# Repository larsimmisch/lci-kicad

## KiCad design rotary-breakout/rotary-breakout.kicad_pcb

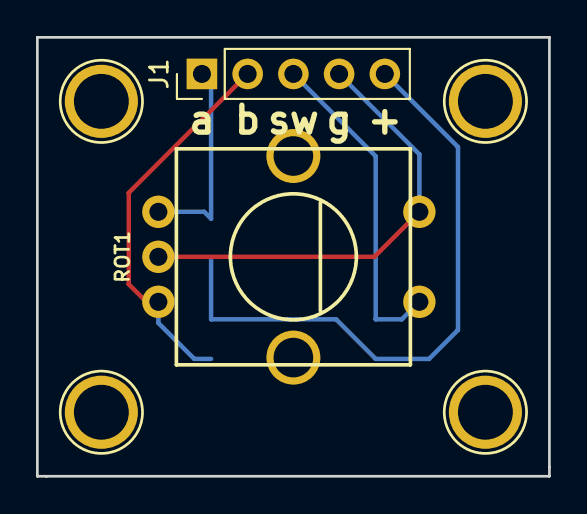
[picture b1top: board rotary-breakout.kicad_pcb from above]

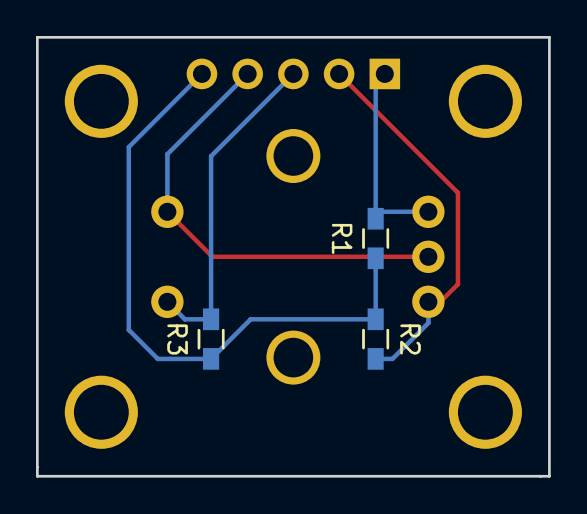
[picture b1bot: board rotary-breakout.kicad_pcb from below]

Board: 2 copper layers, 28.4 x 24.4 mm, 5 parts (3 on the bottom side), 5 nets.

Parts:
J1: CONN_01X05; Pin_Header_Straight_1x05_Pitch2.54mm
R1, R2, R3: R_Small; R_0603_HandSoldering
ROT1: Alps-Rotary-Encoder

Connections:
GND: J1.4, ROT1.1, ROT1.3
unnamed: J1.1, R1.2, ROT1.2
unnamed: J1.2, R2.2, ROT1.4
unnamed: J1.3, R3.2, ROT1.5
VCC: J1.5, R1.1, R2.1, R3.1

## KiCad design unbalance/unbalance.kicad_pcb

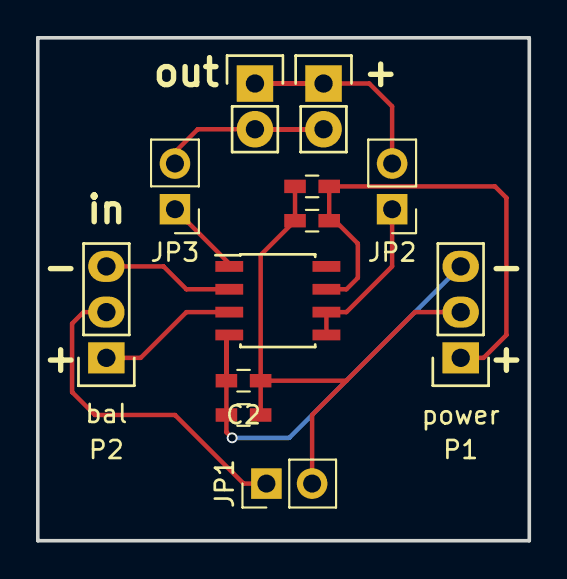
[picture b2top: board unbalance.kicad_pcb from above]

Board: 2 copper layers, 27.3 x 27.9 mm, 12 parts (0 on the bottom side), 10 nets.

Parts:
C1, C2: 1uF; C_0603_HandSoldering
C3, C4: 10uF; C_0603_HandSoldering
JP1: gnd lift; Pin_Header_Straight_1x02_Pitch2.54mm
JP2, JP3: Jumper_NC_Small; Pin_Header_Straight_1x02_Pitch2.54mm
P1: power; Pin_Header_Straight_1x03
P2: bal; Pin_Header_Straight_1x03
P3, P4: CONN_01X02; Pin_Header_Straight_1x02
U1: INA134; SOIC-8_3.9x4.9mm_Pitch1.27mm

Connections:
+15V: C1.1, C3.1, P1.1, U1.7
-15V: C2.2, C4.1, P1.3, U1.4
GNDA: C1.2, C2.1, C3.2, C4.2, JP1.2, P1.2
unnamed: JP1.1, P2.2
unnamed: JP2.1, U1.5, U1.6
unnamed: JP2.2, P3.1, P4.1
unnamed: JP3.1, U1.1
unnamed: JP3.2, P3.2, P4.2
unnamed: P2.1, U1.3
unnamed: P2.3, U1.2

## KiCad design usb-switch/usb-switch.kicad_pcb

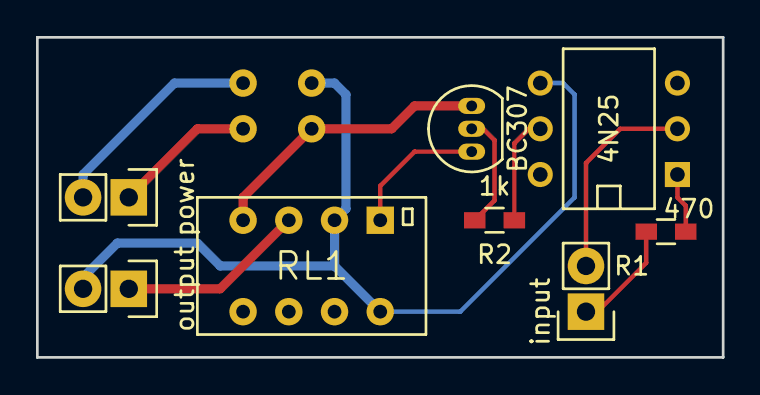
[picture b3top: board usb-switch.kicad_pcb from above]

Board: 2 copper layers, 38.1 x 17.8 mm, 9 parts (0 on the bottom side), 11 nets.

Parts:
FB1: Double_choke; double_choke
IC1: 4N25; DIP-6__300
P1: input; Pin_Header_Straight_1x02
P2: power; Pin_Header_Straight_1x02
P3: output; Pin_Header_Straight_1x02
Q1: BC307; TO-92_Inline_Narrow_Oval
R1: 470; R_0603_HandSoldering
R2: 1k; R_0603_HandSoldering
RL1: Omron_G6K; Omron-G6K

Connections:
+5V: FB1.1, Q1.3, RL1.4
GND: FB1.2, IC1.4, P3.2, RL1.2, RL1.8
unnamed: FB1.3, P2.1
unnamed: FB1.4, P2.2
unnamed: IC1.1, R1.1
unnamed: IC1.2, P1.2
unnamed: IC1.5, R2.1
unnamed: P1.1, R1.2
unnamed: P3.1, RL1.3
unnamed: Q1.1, RL1.1
unnamed: Q1.2, R2.2

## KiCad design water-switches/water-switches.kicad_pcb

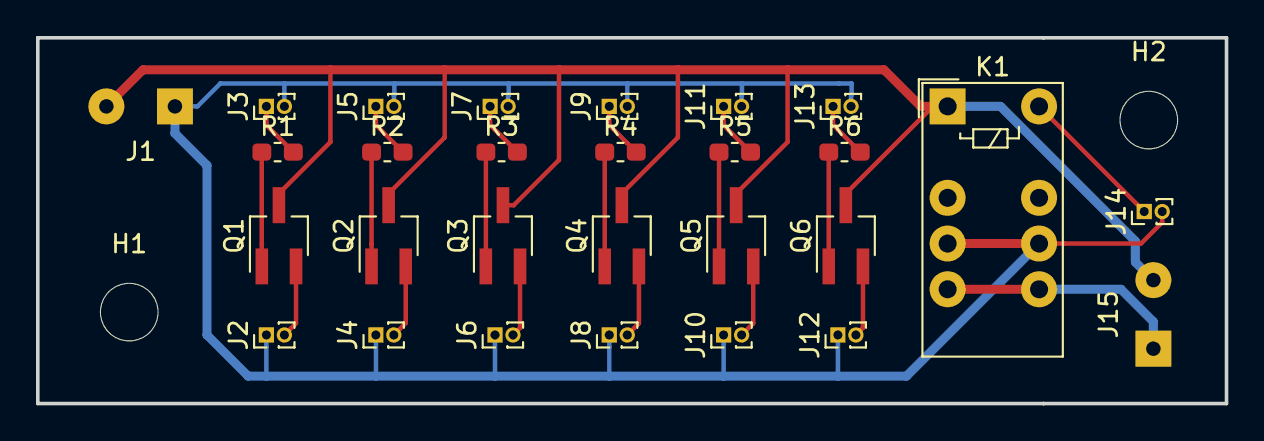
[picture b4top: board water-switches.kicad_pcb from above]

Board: 2 copper layers, 66.0 x 20.3 mm, 30 parts (0 on the bottom side), 22 nets.

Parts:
H1, H2: MountingHole; MountingHole_3.2mm_M3_DIN965
J1: PWR; SolderWirePad_1x02_P3.81mm_Drill0.8mm
J2: Out0; PinHeader_1x02_P1.00mm_Vertical
J3: In0; PinHeader_1x02_P1.00mm_Vertical
J4: Out1; PinHeader_1x02_P1.00mm_Vertical
J5: IN1; PinHeader_1x02_P1.00mm_Vertical
J6: Out2; PinHeader_1x02_P1.00mm_Vertical
J7: IN2; PinHeader_1x02_P1.00mm_Vertical
J8: Out3; PinHeader_1x02_P1.00mm_Vertical
J9: In3; PinHeader_1x02_P1.00mm_Vertical
J10: Out4; PinHeader_1x02_P1.00mm_Vertical
J11: In4; PinHeader_1x02_P1.00mm_Vertical
J12: Out5; PinHeader_1x02_P1.00mm_Vertical
J13: In5; PinHeader_1x02_P1.00mm_Vertical
J14: In6; PinHeader_1x02_P1.00mm_Vertical
J15: Out6; SolderWirePad_1x02_P3.81mm_Drill0.8mm
K1: G6S-2; Relay_DPDT_Omron_G6S-2
Q1, Q2, Q3, Q4, Q5, Q6: Q_NPN_BCE; SOT-23W_Handsoldering
R1, R2, R3, R4, R5, R6: R_Small; R_0603_1608Metric_Pad1.05x0.95mm_HandSolder

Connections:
+12V: J1.1, J2.1, J3.2, J4.1, J5.2, J6.1, J7.2, J8.1, J9.2, J10.1, J11.2, J12.1, J13.2, J14.2, K1.4, K1.7
GND: J1.2, J15.2, K1.1, Q1.3, Q2.3, Q3.3, Q4.3, Q5.3, Q6.3
unnamed: J2.2, Q1.2
unnamed: J3.1, R1.2
unnamed: J4.2, Q2.2
unnamed: J5.1, R2.2
unnamed: J6.2, Q3.2
unnamed: J7.1, R3.2
unnamed: J8.2, Q4.2
unnamed: J9.1, R4.2
unnamed: J10.2, Q5.2
unnamed: J11.1, R5.2
unnamed: J12.2, Q6.2
unnamed: J13.1, R6.2
unnamed: J14.1, K1.10
unnamed: J15.1, K1.5, K1.6
unnamed: Q1.1, R1.1
unnamed: Q2.1, R2.1
unnamed: Q3.1, R3.1
unnamed: Q4.1, R4.1
unnamed: Q5.1, R5.1
unnamed: Q6.1, R6.1
